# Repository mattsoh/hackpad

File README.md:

# Hackpad

The Matthew Hackpad for Hack Club Highway. Got a lot of buttons and rotating stuff

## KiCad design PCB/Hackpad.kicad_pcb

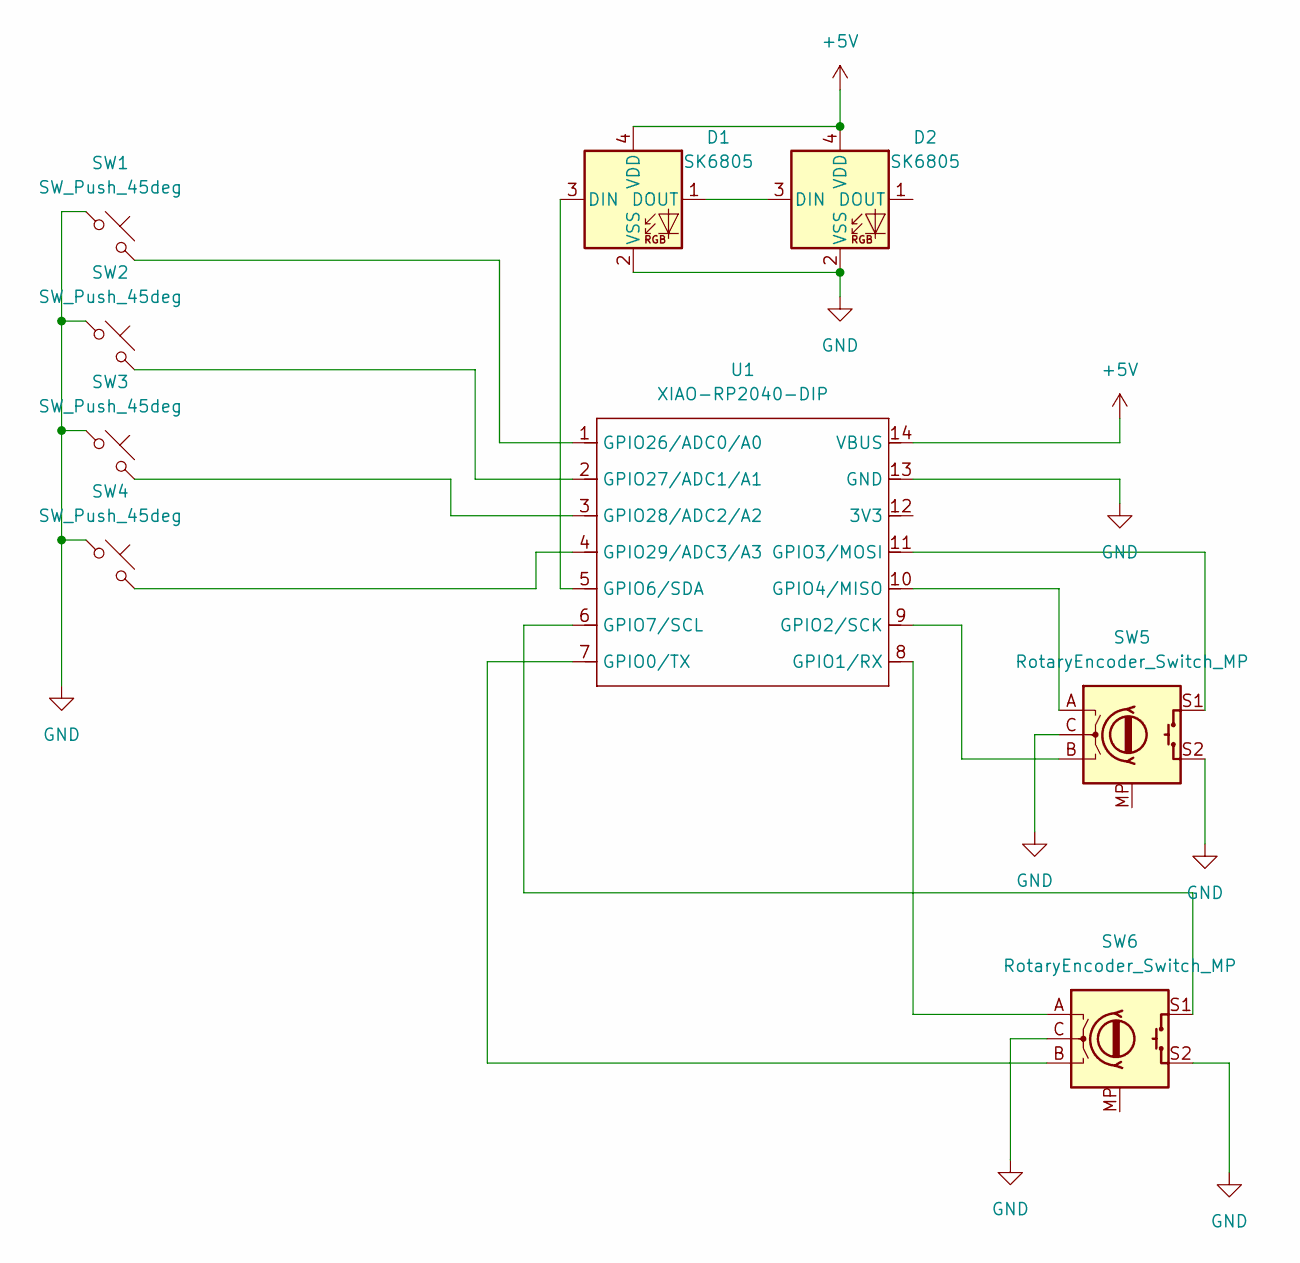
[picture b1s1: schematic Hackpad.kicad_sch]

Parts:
D1, D2: SK6805; LED_SK6805_PLCC4_2.4x2.7mm_P1.3mm
SW1, SW2, SW3, SW4: SW_Push_45deg; SW_Cherry_MX_PCB_1.00u
SW5, SW6: RotaryEncoder_Switch_MP; RotaryEncoder_Alps_EC11E-Switch_Vertical_H20mm_CircularMoun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
U1: XIAO-RP2040-DIP; MOUDLE14P-XIAO-DIP-SMD

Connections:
+5V: D1.4 (VDD), D2.4 (VDD), U1.14 (VBUS)
GND: D1.2 (VSS), D2.2 (VSS), SW1.1, SW2.1, SW3.1, SW4.1, SW5.C, SW5.S2, SW6.C, SW6.S2, U1.13 (GND)
unnamed: D1.3 (DIN), U1.5 (GPIO6/SDA)
unnamed: D1.1 (DOUT), D2.3 (DIN)
unnamed: SW6.B, U1.7 (GPIO0/TX)
unnamed: SW6.A, U1.8 (GPIO1/RX)
unnamed: SW5.B, U1.9 (GPIO2/SCK)
unnamed: SW5.S1, U1.11 (GPIO3/MOSI)
unnamed: SW5.A, U1.10 (GPIO4/MISO)
unnamed: SW6.S1, U1.6 (GPIO7/SCL)
unnamed: SW1.2, U1.1 (GPIO26/ADC0/A0)
unnamed: SW2.2, U1.2 (GPIO27/ADC1/A1)
unnamed: SW3.2, U1.3 (GPIO28/ADC2/A2)
unnamed: SW4.2, U1.4 (GPIO29/ADC3/A3)

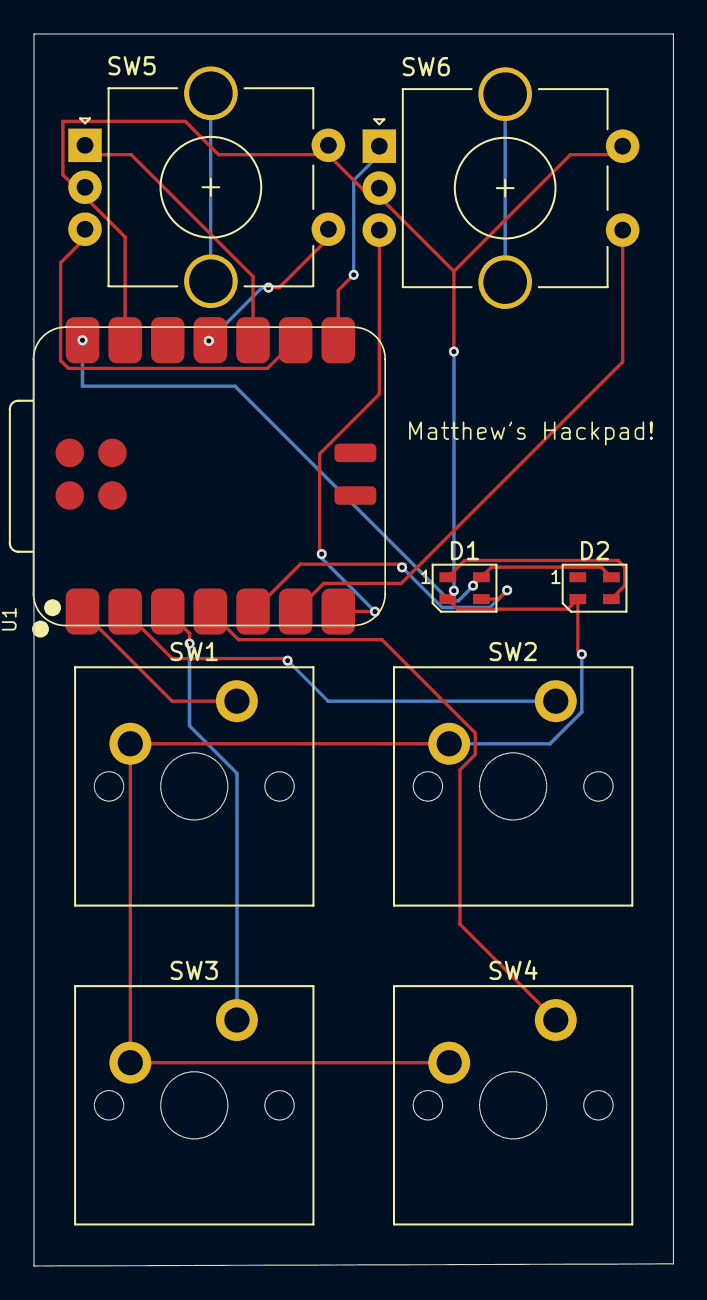
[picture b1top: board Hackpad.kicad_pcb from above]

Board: 2 copper layers, 38.1 x 73.4 mm, 9 parts (0 on the bottom side), 14 nets.

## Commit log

2025-07-11 Fixing stuff
2025-07-12 fix changes
